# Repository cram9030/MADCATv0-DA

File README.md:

# MADCATv0-DA
Code base for MADCAT version 0 data aquisition

This project will be using the Beaglebone Black and LSM9DS1 sesnor. 

The code to interact with the LSM9DS1 was adapted from https://github.com/sparkfun/SparkFun_LSM9DS1_Arduino_Library

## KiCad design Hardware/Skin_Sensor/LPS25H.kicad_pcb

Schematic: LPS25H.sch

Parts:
C1, C2, C4, C5, C6: 1UF; C_0402
C3, C10, C14, C28: 100nF; C_0603
C7, C8: 22pF; C_0402
C9, C13: 4.7UF; C_0603
C11, C15: sj2; SJ-2-1-no
C12: sj1; SJ-2-1-no
C16, C17, C18: WM1386x06; WM1387x06-REC
C19: 10uF; C_0402
C20, C21, C23: 100nF; C_0402
C22: 10nF; C_0402
C24, C25: 1uF; C_0402
C26, C27: 0.47uF; C_0402
D1: LED; LED_0402
D2: LED_RGB_CC; 4-PLCC
L1, L2: LPS25H
P1: CONN_01X05; 2.54mmX05
R1: 330; R_0402
R2, R3, R4, R5, R6, R7, R8, R9, R10, R11, R12, R13: 10k; R_0402
R14: 100k; R_0402
SW1: SW_PUSH; SPST-NO-TL3700
U1: ADP7102; DFN-8-1EP_3x3mm_Pitch0.5mm
U2: ATSAMD21E18A; QFN-32-1EP_5x5mm_Pitch0.5mm
U3: AVRISP; TagConnectx06
U4: LSM9DS1
U5: LP5521YQ; QFN-24-1EP_4x5mm_Pitch0.5mm
U6: DPS310; 8-LGA
X1: ABS06

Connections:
+3V3: C4.2, C6.1, C9.1, C10.1, C13.1, C14.1, C19.1, C20.1, C21.1, C24.1, L1.1 (VDD_IO), L1.10 (VDD), L2.1 (VDD_IO), L2.10 (VDD), R1.1, R2.1, R3.1, R4.1, R5.1, R7.1, R8.1, R9.1, R10.1, R11.1, R12.1, R13.1, U1.2 (SEN/ADJ), U1.5 (EN/UVLO), U1.8 (VIN), U2.9 (VDDANA), U2.30 (VDDIN), U3.2 (VCC), U4.1 (VDDIO), U4.3 (VDDIO), U4.22 (VDD), U4.23 (VDD), U5.3 (VDD)
AREF: C5.1, U2.4 (PA03/VREFA/AIN1)
D+: C12.3, U2.24 (PA25/SC33/SCA53)
D-: C11.3, U2.23 (PA24/SC32/SCA52)
DI0: C18.3, U2.5 (VREFB/PA04/AIN4/ACIN0/SCA00)
DI1: C17.3, U2.17 (PA16/SC10/SCA30)
DI2: C16.3, U2.11 (PA08/NMI/AIN16/SC00/SCA20)
DO0: C18.4, U2.6 (PA05/AIN5/ACIN1/SCA01)
DO1: C17.4, U2.18 (PA17/SC11/SCA31)
DO2: C16.4, U2.12 (PA09/AIN17/SC01/SCA21)
GND: C1.2, C2.2, C4.1, C5.2, C6.2, C7.1, C8.1, C9.2, C10.2, C13.2, C14.2, C16.1, C16.6, C16.7, C17.1, C17.6, C17.7, C18.1, C18.6, C18.7, C19.2, C20.2, C21.2, C22.2, C23.2, C24.2, C25.2, D1.2 (K), D2.4 (COMMON_CATHODE), L1.3, L1.8 (GND), L1.9, L2.3, L2.8 (GND), L2.9, R6.2, SW1.1, SW1.2, U1.3 (GND), U1.6 (GND), U1.9 (GND), U2.10 (GND), U2.28 (GND), U2.33 (GND), U3.6 (GND), U4.14 (RES), U4.15 (RES), U4.16 (RES), U4.17 (RES), U4.18 (RES), U4.19 (GND), U4.20 (GND), U5.4 (GND), U5.5 (CLK_32K), U5.7 (TRIG), U5.20 (ASEL0), U5.21 (ASEL1), U5.25 (GND)
GND_EX: C3.2, C28.1, P1.5, R14.2, U6.1 (GND), U6.7 (GND)
INT_EX: C15.2, P1.4
L1_INT: L1.7 (INT1)
L2_INT: L2.7 (INT1)
unnamed: C7.2, U2.1 (XIN32/PA00/SCA10), X1.1
unnamed: C8.2, U2.2 (XOUT32/PA01/SCA11), X1.2
unnamed: C11.1, U3.1 (MISO)
unnamed: C12.1, U3.3 (SCK)
unnamed: C15.1, U6.5 (SDO)
unnamed: C15.3, R14.1
unnamed: C22.1, U4.21 (CAP)
unnamed: C23.1, U4.24 (C1)
unnamed: C25.1, U5.22 (VOUT)
unnamed: C26.1, U5.1 (CF2+)
unnamed: C26.2, U5.23 (CF2-)
unnamed: C27.1, U5.2 (CF1+)
unnamed: C27.2, U5.24 (CF1-)
unnamed: D1.1 (A), R1.2
unnamed: D2.1 (RED_ANODE), U5.17 (R)
unnamed: D2.2 (GREEN_ANODE), U5.18 (G)
unnamed: D2.3 (BLUE_ANODE), U5.19 (B)
unnamed: L1.5 (SA0/MISO), R4.2
unnamed: L1.6 (CS), R5.2
unnamed: L2.5 (SA0/MISO), R6.1
unnamed: L2.6 (CS), R7.2
unnamed: R8.2, U4.5 (SDO_A/G)
unnamed: R9.2, U4.7 (CS_A/G)
unnamed: R10.2, U4.6 (SDO_M)
unnamed: R11.2, U4.8 (CS_M)
unnamed: R12.2, U5.14 (EN)
unnamed: R13.2, U5.6 (INT)
RESET: SW1.3, SW1.4, U2.26 (RESET), U3.5 (RST/)
SCL: L1.2 (SCL/SCK), L2.2 (SCL/SCK), R2.2, U2.22 (PA23/SC31/SCA51), U4.2 (SCL/SPC), U5.15 (SCL)
SCL_EX: P1.3, U6.4 (SCK)
SDA: L1.4 (SDA/MOSI), L2.4 (SDA/MOSI), R3.2, U2.21 (PA22/SC30/SCA50), U4.4 (SDA/SDI/SDO), U5.13 (SDA)
SDA_EX: P1.2, U6.3 (SDI)
SWCLK: C12.2, U2.31 (PA30/SWCLK/SCA12)
SWDIO: C11.2, U2.32 (PA31/SWDIO/SCA13)
VDDCORE: C2.1, U2.29 (VDDCORE)
VDD_EX: C3.1, C28.2, P1.1, U6.6 (VDDIO), U6.8 (VDD)
VRAW: C1.1, C16.2, C16.5, C17.2, C17.5, C18.2, C18.5, U1.1 (VOUT), U3.4 (MOSI)

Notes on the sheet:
Power
Microcontroller
R-Series Compatibility:
Avoid pins 3,5,6,11-14,21,24
Comms
NB: USB is 22/23 on R-Series
Sensors
NB: Reusing Tag Connect as USB & JTAG
Status LED
I2C Addr: 0x5d
I2C Addr: 0x5c
AG Addr: 0x6B
M Addr: 0x1E
Testing A New Sensor

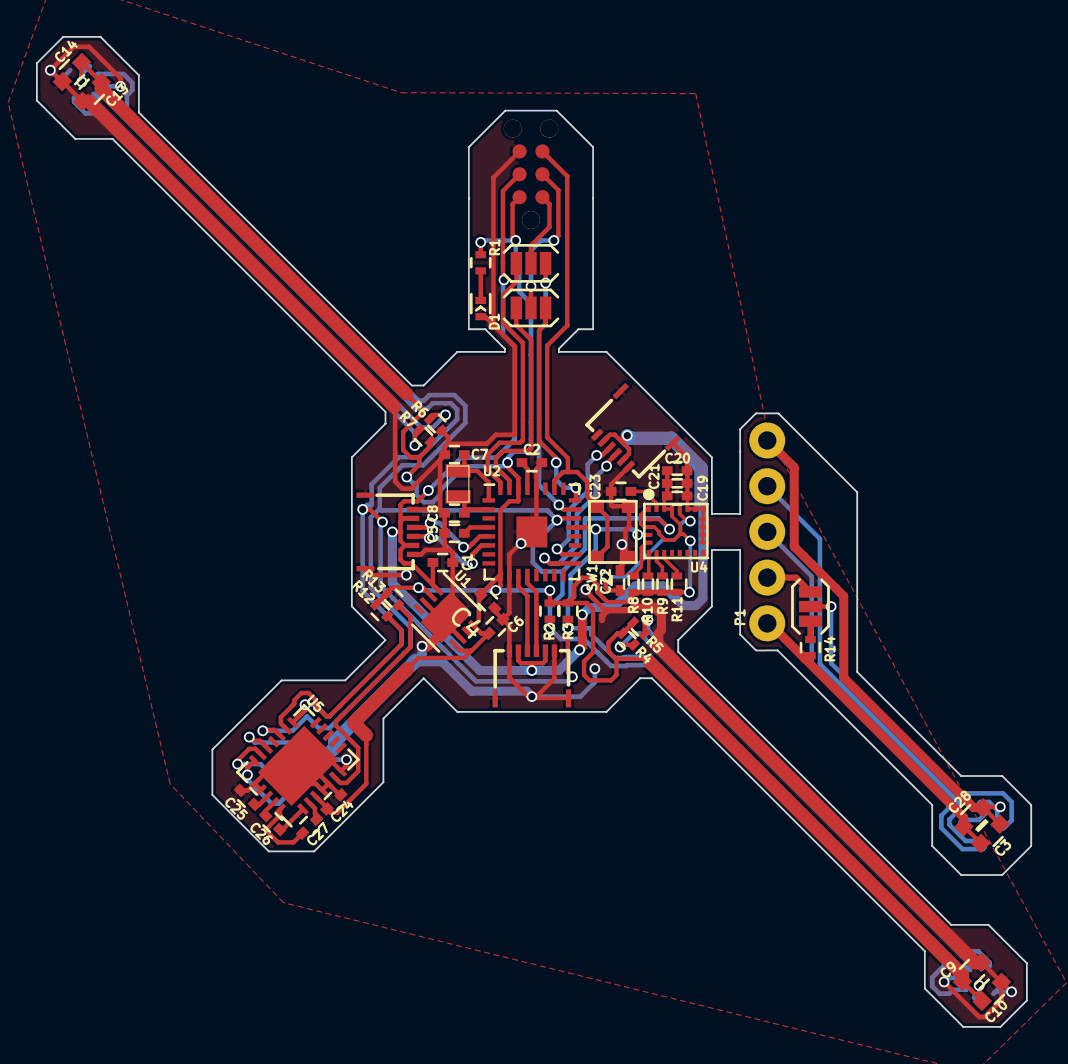
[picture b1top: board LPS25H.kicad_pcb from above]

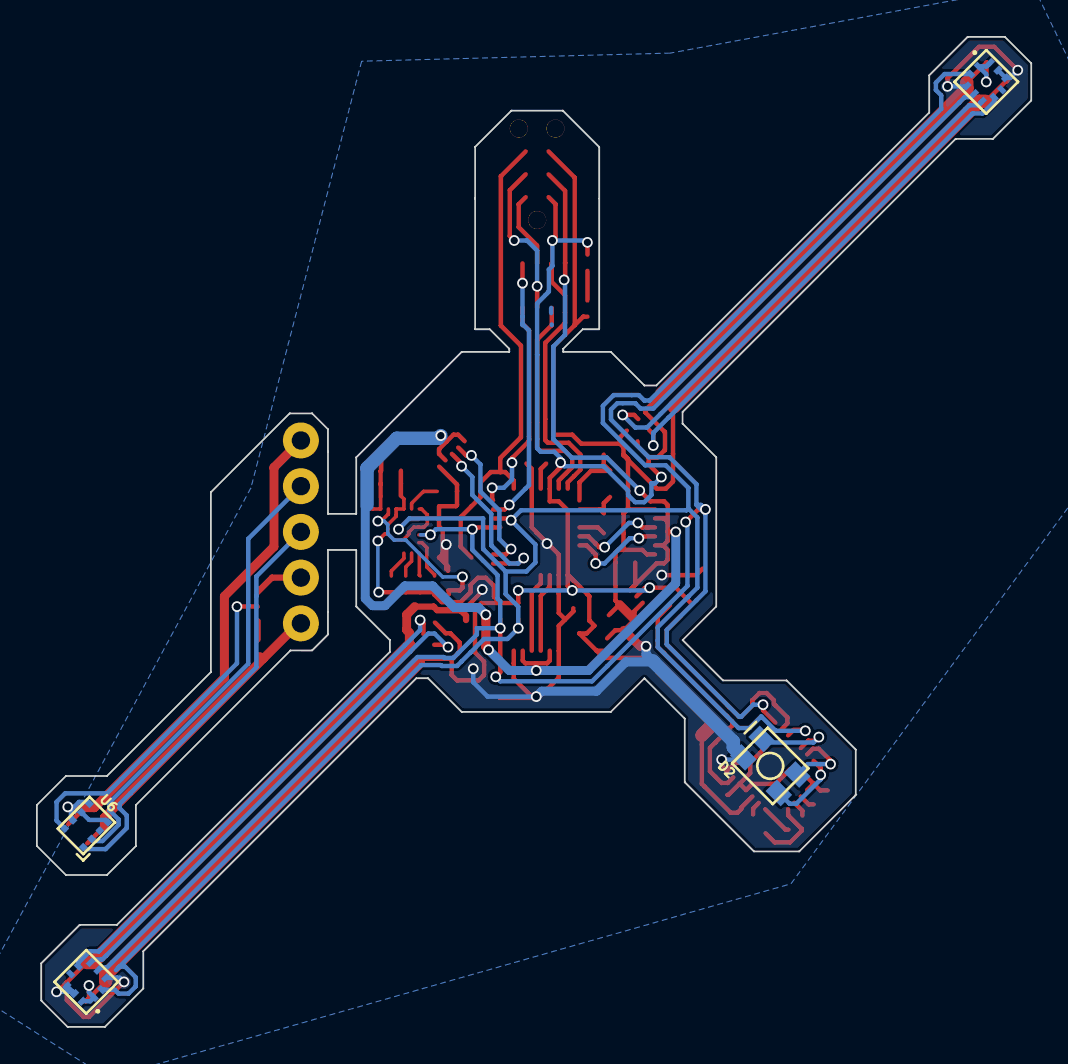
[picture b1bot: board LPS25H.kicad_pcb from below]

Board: 2 copper layers, 55.2 x 55.0 mm, 55 parts (4 on the bottom side), 50 nets.

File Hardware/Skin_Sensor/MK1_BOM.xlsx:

Reference Designator | Quantity | Description/Value | Manufacturer Part Number (MPN)
C1,C2,C4,C5,C6,C24,C25 | 7 | 0402 Cer Cap 1uF | C1005X5R1V105K050BC
C7,C8 | 2 | 0402 Cer Cap 22pF | CBR04C220F5GAC
C9,C13 | 2 | 0603 Cer Cap 4.7uF | GRM188R61A475KE15D
C3,C10,C14,C28 | 4 | 0603 Cer Cap 100nF | GRM188R71E104KA01D
C19 | 1 | 0402 Cer Cap 10uF | CL05A106MP8NUB8
C20,C21,C23 | 3 | 0402 Cer Cap 100nF | GRM155R71C104KA88J
C26,C27 | 2 | 0402 Cer Cap 0.47uF | C1005X5R1E474K050BB
R1 | 1 | 0402 Res 330 | RC0402JR-07330RL
R2,R3,R4,R5,R6,R7,R8,R9,R10,R11,R12,R13 | 12 | 0402 Res 10k | RC0402JR-0710KL
R14 | 1 | 0402 Res 100k | RC0402JR-07100KL
D1 | 1 | 0402 LED | LNJ247W82RA
D2 | 1 | RGB LED Common Cathode | XZM2CRKM2DGFBB45SCCB
C16,C17,C18 | 3 | WM1387 Plug | 5034800600
L1,L2 | 2 | LPS25HB Pressure Sensor | LPS25HBTR
SW1 | 1 | Switch | TL3700AF100QG
U1 | 1 | ADP7102 3.3V Reg | ADP7102ACPZ-3.3-R7
U2 | 1 | ATSAMD21E18A uP | ATSAMD21E18A-MFT
U4 | 1 | LSM9DS1 IMU | LSM9DS1TR
U5 | 1 | LP5521YQ LED Driver | LP5521YQ/NOPB
U6 | 1 | DPS310 Pressure Sensor | DPS310XTSA1
X1 | 1 | 32.768kHz Crystal | ABS06-32.768KHZ-1-T

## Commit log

2016-06-14 :lollipop: Added .gitattributes & .gitignore files
2016-06-15 Initial commit
    These files in the include are meant to communicate to the LSM9DS1
    sensor and are based off the code from
    https://github.com/sparkfun/SparkFun_LSM9DS1_Arduino_Library
    This has not been compiled or tested in any way yet
2016-06-16 Added test file
    Everything compiles but the test outputs the same wrong values everytime
2016-06-17 Single testing is working
2016-06-20 Updated I2CreadBytes
    It now reads multiple bytes at a time
2016-06-20 Created reading 2 axis accel and gyro reading functions
    This increases the read time of two axis if the two axis being accessed
    are in adjacent registers
2016-06-21 added spi library
2016-06-21 implemented spi
2016-06-21 changed test to test spi
2016-06-21 Deleted who am I print
2016-06-21 it compiles
2016-06-22 Corrected the bus address SPI now initialized
2016-06-23 SPI communication is working now
    SPI mode is 0 and the chip select pin for the Mag needs to be tied high
2016-06-23 Updated SPI Speed
2016-06-23 Trying to get SPIreadBytes to work
    printing data shows that they are all the same
2016-06-24 Commiting to revert
2016-06-24 Revert "Updated SPI Speed"
    This reverts commit 54cf3980477879e2225a32491cb75498a3efa604.
2016-06-24 commit to revert
2016-06-24 SPI read is working now
    Though gravity is 1/3 what it should be. This still needs to be
    addressed
2016-06-24 Added Hardware folder and software folder
2016-06-24 Actually added hardware folder
2016-06-24 uncommented while(1)
2016-06-24 Corrected the SpiDevice.h files
2016-06-25 added flip flop code
2016-06-28 updated test code
2016-06-28 Commiting to branch
2016-06-28 Updated and fixed Spi communications
    The issues mostly arose from the fact that initMag() was still running
    even when the Mag was disabled resulting in the Accel registers getting
    reset
2016-06-28 Fixed table
2016-06-28 Unbolding pin line
2016-06-28 Added P9 header
2016-06-28 Formatting
2016-06-28 added second imu.begin()
2016-06-29 added some initialization for the flip flops. Still doesn't work
2016-06-29 More formating
2016-06-29 test code without gpio
2016-06-30 added separate if statements for initializing imus
2016-07-01 added 4th imu
2016-07-01 sampling with 4 imus
2016-07-06 BeagleBone Black Shield and Board
2016-07-07 Complete routing for cape
    Also updated the schematic just calling out the ground connections
2016-07-07 Updated switch lay out and routing
2016-07-08 tests 7 sensors now reading both the accel and gyro from each. Data is saved in testing.txt
2016-07-09 Rev 3 IMU Board
    Here it is, in all its glory.
2016-07-09 Added Indicator LED
2016-07-09 Corrected Position for GPS headers
2016-07-11 updated trace widths on cape
2016-07-11 created the images for the modela
2016-07-11 Added CAM Files
2016-07-12 Fixed the headers for the M08 cables coming from the IMU
2016-07-12 Cleaned up some of the traces
2016-07-12 updated cam
2016-07-13 added gps code
2016-07-13 created png for updated cape
2016-07-15 Split cape into two components
    Lower layer is the GPS and Pot and upper layer is the SPI connections
2016-07-16 added mk1 LPS25H hardware
2016-07-19 hot, warm, and cold start code for gps
2016-07-19 Added High Sensitivity Mode for the GPS
2016-07-20 LPS25H MK II
2016-07-22 Commit for merge
2016-07-24 added cam info (for a flex order)
2016-08-09 Added code for APA with BBB bit banging
    This code has not even been compiled yet. First push for revert
    purposes.
2016-08-10 it's been a while since my last commit but this is the tiny board eagle files
2016-08-10 Updated APA protocol so now everything compiles
    THIS HAS NOT BEEN TESTED YET
    compile command for BBB
    g++ -pthread Include/GPIO.cpp Include/BBBDigitialIOAPA.cpp
    Include/APAProtocol.cpp test/APABBBtest.cpp -o APABBtest -w
2016-08-15 Small changes - commit just to checkout other branch
2016-08-22 APABBtest.cpp compiles
    I am still unsure if I want to remove the protocol class and just make
    it an library and a data structure. I think that will be better but this
    commit is to just have refrence of the class structure.
2016-08-23 APA still not working
    For some reason the GPIO class does not seem to be working correctly
    once intialized outside the intialization function. I am suspending work
    on this and focusing on the reading the analog values. This reqires
    recreating the analog cape.
2016-08-30 Added GPS test
    It works!
2016-08-30 i think this is just the final version of the tiny but there might be more, it's been a while since I commited
2016-08-30 git told me to commit
2016-08-30 created images for mill for bbb cape
2016-09-02 working version of the adc/gps cape
2016-09-07 many iterations of the spi-ff cape
2016-09-07 you'll never guess, more updates to the cape!
2016-09-16 Quick update to power budget
2016-11-16 Added ADC codes and spi device tree
2016-11-21 Testing reading of the string pots
2016-11-22 Flight Test Compiles
2016-11-23 Updated Flight test slightly
    Just added simple commandline functionality
2016-11-24 Final update for flight testing on 11/23/2016
2016-12-22 V1 Skin Sensor
2016-12-22 Fixed pour issues
2016-12-27 Added sensor and cleaned up the board
2017-01-04 Modular skin sensor (mk 2, rigid board)
2017-02-15 Added calibration code
